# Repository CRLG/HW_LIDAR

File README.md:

# HW_LIDAR
Carte électronique du LIDAR CRLG

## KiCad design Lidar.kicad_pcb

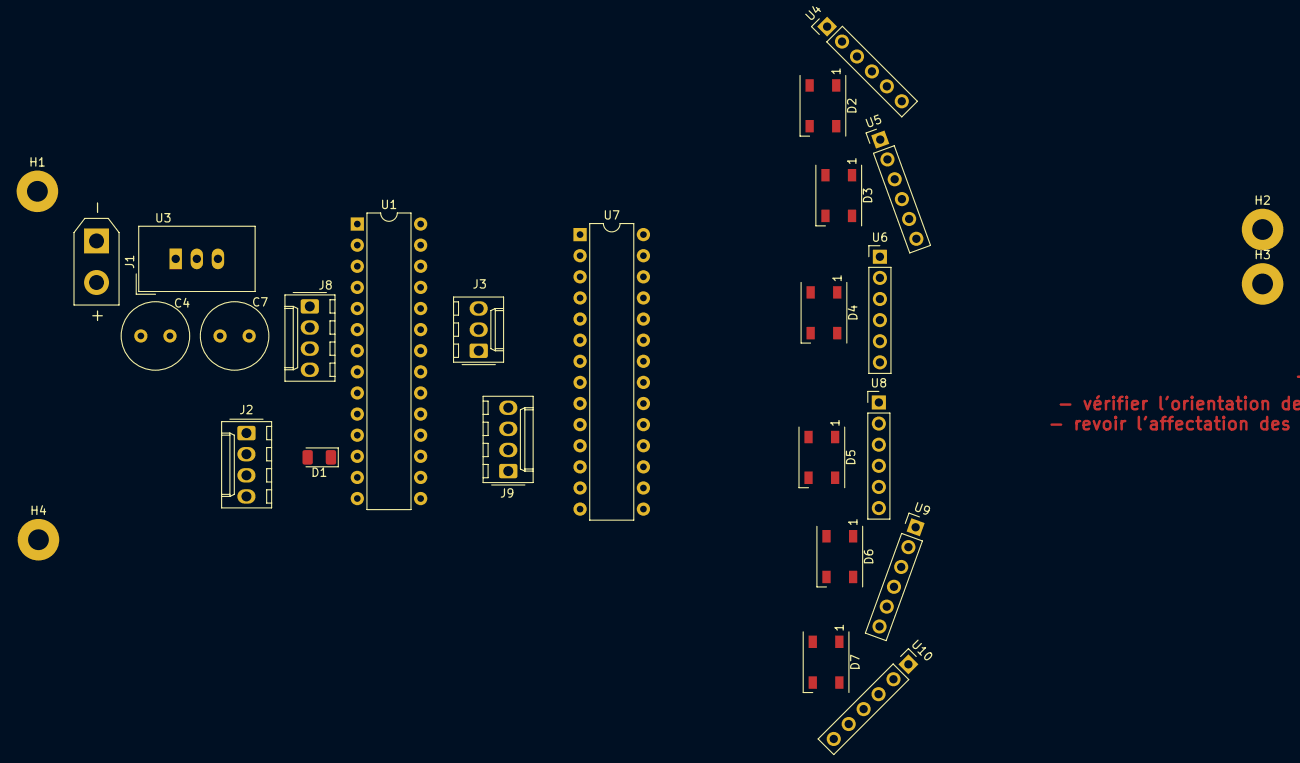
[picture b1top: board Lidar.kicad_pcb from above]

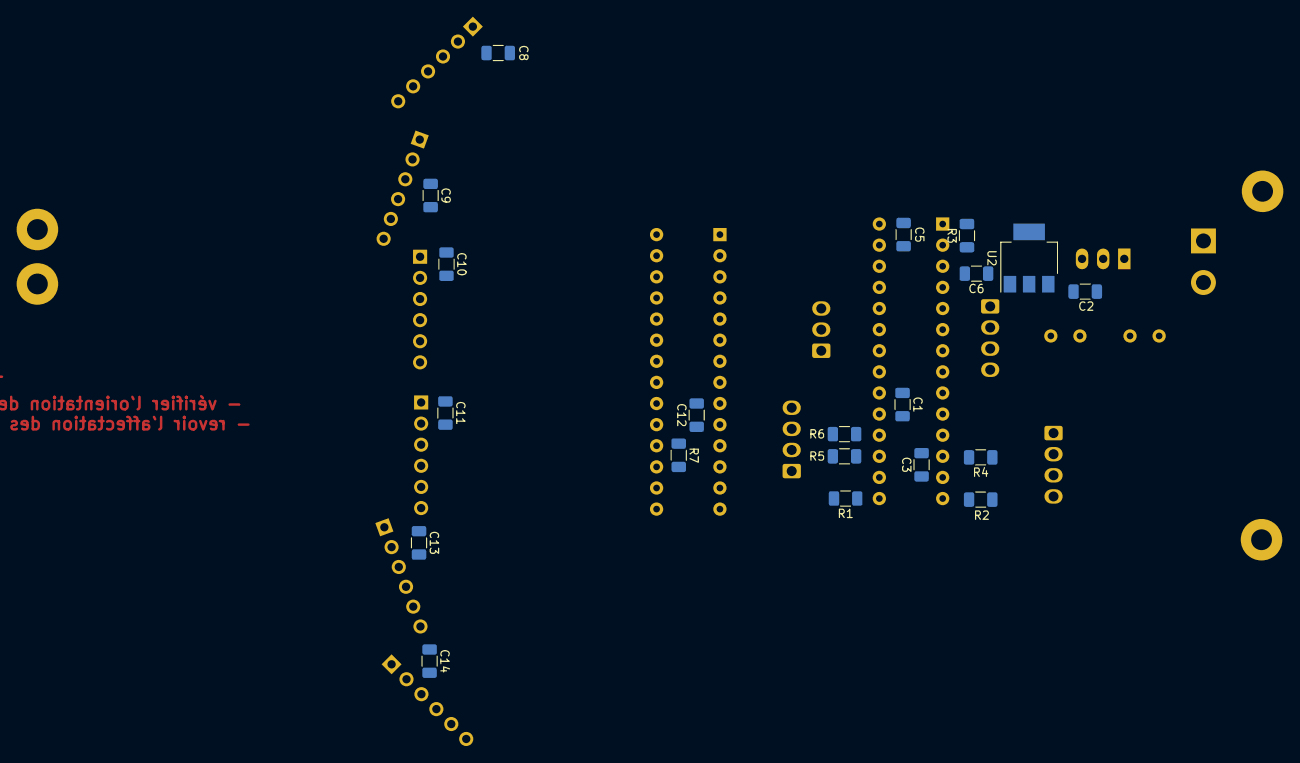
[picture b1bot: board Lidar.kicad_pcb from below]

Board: 2 copper layers, 47 parts (20 on the bottom side), 29 nets, no tracks yet.

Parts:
C1: 10u; C_1206_3216Metric
C2, C6: 1u; C_1206_3216Metric
C3, C5, C8, C9, C10, C11, C12, C13, C14: 100n; C_1206_3216Metric
C4, C7: 220u; C_Radial_D8.0mm_H11.5mm_P3.50mm
D1: LED; LED_1206_3216Metric
D2, D3, D4, D5, D6, D7: WS2812B; LED_WS2812B_PLCC4_5.0x5.0mm_P3.2mm
H1, H2, H3, H4: MountingHole_Pad; MountingHole_2.5mm_Pad
J1: Conn_XT30; AMASS_XT30UPB-M_1x02_P5.0mm_Vertical
J2, J8, J9: Conn_01x04; Molex_KK-254_AE-6410-04A_1x04_P2.54mm_Vertical
J3: Conn_01x03; Molex_KK-254_AE-6410-03A_1x03_P2.54mm_Vertical
R1, R2, R5, R6: 4.7k; R_1206_3216Metric
R3, R7: 10k; R_1206_3216Metric
R4: 470; R_1206_3216Metric
U1: DSPIC33EP256GP502; DIP-28_W7.62mm
U2: MCP1804x-3302xDB; SOT-223-3_TabPin2
U3: TSR_2-2450; Converter_DCDC_TRACO_TSR-2_THT
U4, U5, U6, U8, U9, U10: VL53L0X; VL53L0x_1x06_P2.54mm_Vertical
U7: MCP23017_SP; DIP-28_W7.62mm

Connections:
+5V: C2.1, C7.1, C8.1, C9.1, C10.1, C11.1, C12.2, C13.1, C14.1, D2.1, D3.1, D4.1, D5.1, D6.1, D7.1, J2.4, J9.4, R7.1, U2.3, U3.3, U4.1, U5.1, U6.1, U7.9, U8.1, U9.1, U10.1
/3.3V_dsPIC: C3.1, C5.2, C6.1, R1.2, R2.2, R3.1, R5.2, R6.2, U1.13, U1.28, U2.1
/I2C_master_SCL: J2.2, R1.1, U1.15, U4.3, U5.3, U6.3, U7.12, U8.3, U9.3, U10.3
/I2C_master_SDA: J2.3, R2.1, U1.14, U4.4, U5.4, U6.4, U7.13, U8.4, U9.4, U10.4
/I2C_slave_SCL: J9.2, R5.1, U1.17
/I2C_slave_SDA: J9.3, R6.1, U1.18
/UARTdbg_Rx: J3.2, U1.23
/UARTdbg_Tx: J3.1, U1.22
/VBAT: C4.1, J1.2, U3.1
/XSHUT_1: U4.6, U7.21
/XSHUT_2: U5.6, U7.22
/XSHUT_3: U6.6, U7.23
/XSHUT_4: U7.24, U8.6
/XSHUT_5: U7.25, U9.6
/XSHUT_6: U7.26, U10.6
/dsPIC_MCLR: J8.1, R3.2, U1.1
/dsPIC_PGEC: J8.3, U1.5
/dsPIC_PGED: J8.2, U1.4
/ws2812b_data: D2.4, U1.21
GND: C1.2, C2.2, C3.2, C4.2, C5.1, C6.2, C7.2, C8.2, C9.2, C10.2, C11.2, C12.1, C13.2, C14.2, D1.1, D2.3, D3.3, D4.3, D5.3, D6.3, D7.3, H1.1, H2.1, H3.1, H4.1, J1.1, J2.1, J3.3, J8.4, J9.1, U1.8, U1.19, U1.27, U2.2, U3.2, U4.2, U5.2, U6.2, U7.10, U7.15, U7.16, U7.17, U8.2, U9.2, U10.2
unnamed: C1.1, U1.20
unnamed: D1.2, R4.1
unnamed: D2.2, D3.4
unnamed: D3.2, D4.4
unnamed: D4.2, D5.4
unnamed: D5.2, D6.4
unnamed: D6.2, D7.4
unnamed: R4.2, U1.12
unnamed: R7.2, U7.18

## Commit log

2020-11-15 Ajout de KICAD_LIB comme sous module au projet
2020-12-29 Première version du schéma proto
